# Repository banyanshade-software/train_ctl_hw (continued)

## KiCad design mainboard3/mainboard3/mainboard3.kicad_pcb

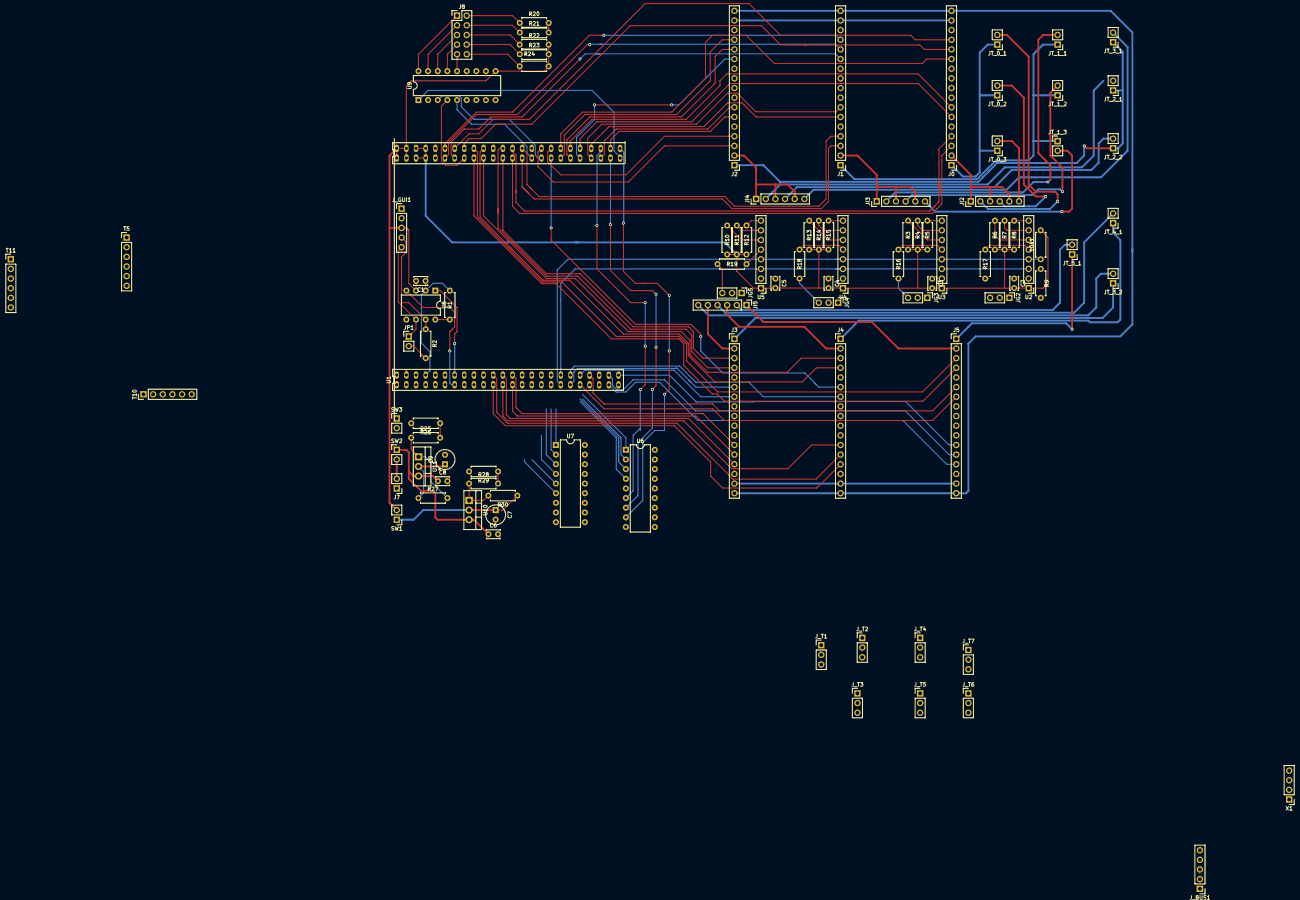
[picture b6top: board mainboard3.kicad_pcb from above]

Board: 2 copper layers, 96 parts (0 on the bottom side), 153 nets.

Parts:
10k1: R; R_Axial_DIN0207_L6.3mm_D2.5mm_P7.62mm_Horizontal
C1, C2, C3, C4, C5: 100nF; C_Disc_D3.4mm_W2.1mm_P2.50mm
C6, C8: 0.1µF; C_Disc_D3.4mm_W2.1mm_P2.50mm
C7, C9: 10µF; CP_Radial_Tantal_D5.0mm_P2.50mm
J0, J1, J2, J3, J4, J5: Conn_01x18; PinHeader_1x17_P2.54mm_Vertical
J7: Conn_01x02_Female; PinHeader_1x02_P2.54mm_Vertical
J8: Conn_02x05_Odd_Even; PinHeader_2x05_P2.54mm_Vertical
JG2, JG3, JG4, JG5: Conn_01x03_Female; PinHeader_1x03_P2.54mm_Vertical
JI2, JI3, JI4, JI5: Conn_01x06_Female; PinHeader_1x06_P2.54mm_Vertical
JP1: Jumper; PinHeader_1x02_P2.54mm_Vertical
JT_0_1, JT_0_2, JT_0_3, JT_1_1, JT_1_2, JT_1_3, JT_2_1, JT_2_2, JT_3_1, JT_3_2, JT_4_1, JT_5_1: Screw_Terminal_01x02; PinHeader_1x02_P2.54mm_Vertical
J_BUS1: Conn_01x05_Female; PinHeader_1x05_P2.54mm_Vertical
J_GUI1: Conn_01x05_Female; PinHeader_1x05_P2.54mm_Vertical
J_T1, J_T2, J_T3, J_T4, J_T5, J_T6, J_T7: Conn_01x03_Female; PinHeader_1x03_P2.54mm_Vertical
R1, R20, R21, R22, R23, R24, R25, R26: R; R_Axial_DIN0207_L6.3mm_D2.5mm_P7.62mm_Horizontal
R2: 120; R_Axial_DIN0207_L6.3mm_D2.5mm_P7.62mm_Horizontal
R3, R4, R5, R6, R7, R8, R9, R10, R11, R12, R13, R14, R15, R16, R17, R18, R19: 10k; R_Axial_DIN0207_L6.3mm_D2.5mm_P7.62mm_Horizontal
R27, R30: 240; R_Axial_DIN0207_L6.3mm_D2.5mm_P7.62mm_Horizontal
R28: 510; R_Axial_DIN0207_L6.3mm_D2.5mm_P7.62mm_Horizontal
R29: 200; R_Axial_DIN0207_L6.3mm_D2.5mm_P7.62mm_Horizontal
SW1, SW2, SW3: SW_DIP_x01; PinHeader_1x02_P2.54mm_Vertical
T5, T10, T11: Screw_Terminal_01x06; PinHeader_1x06_P2.54mm_Vertical
U1: STM32_F4xx; STM32_F4XXrev
U2, U3, U4, U5: ModuleINA3221; PinHeader_1x08_P2.54mm_Vertical
U6, U7, U9: ULN2803A; DIP-18_W7.62mm
U8: MCP2551-I-P; DIP-8_W7.62mm
U10, U11: LM317_TO220; TO-220-3_Vertical
X1: Screw_Terminal_01x04; PinHeader_1x04_P2.54mm_Vertical

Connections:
3V3: 10k1.2, C2.2, C3.2, C4.2, C5.2, R3.1, R4.1, R5.1, R6.1, R7.1, R8.1, R9.2, R10.1, R11.1, R12.1, R13.1, R14.1, R15.1, T10.2, U1.1, U1.2, U1.3, U1.4, U1.53, U1.54, U1.55, U1.56, U2.1, U3.1, U4.1, U5.1
5V: C1.2, J_BUS1.3, J_GUI1.3, R20.2, R21.2, R22.2, R23.2, R24.2, SW1.2, U1.49, U1.50, U1.51, U1.52, U8.3, U9.10, X1.3
12V: J0.17, J1.17, J2.17, J3.17, J4.17, J5.17, J_BUS1.1, J_T1.2, J_T2.2, J_T3.2, J_T4.2, J_T5.2, J_T6.2, J_T7.2, SW3.2, U6.10, U7.10, X1.1
12Vunreg: C6.1, C8.1, SW2.1, U10.3, U11.3
BOARD_LED2: U1.77, U9.5
CAN_RX: U1.13, U8.4
CAN_TX: U1.14, U8.1
CT0_1: J0.12, U1.84
CT0_2: J0.13, U1.64
CT0_3: J0.14, U1.62
CT1_1: J1.12, U1.61
CT1_2: J1.13, U1.59
CT1_3: J1.14, U1.60
CT2_1: J2.12, U1.87
CT2_2: J2.13, U1.85
CT2_3: J2.14, U1.83
CT3_1: J3.12, U1.26
CT3_2: J3.13, U1.25
CT3_3: J3.14, U1.24
CT4_1: J4.12, U1.23
CT4_2: J4.13, U1.22
CT4_3: J4.14, U1.21
CT5_1: J5.12, U1.48
CT5_2: J5.13, U1.46
CT5_3: J5.14, U1.45
GND: C1.1, C2.1, C3.1, C4.1, C5.1, C6.2, C7.2, C8.2, C9.2, J0.16, J1.16, J2.16, J3.16, J4.16, J5.16, J7.1, JG2.1, JG2.2, JG3.1, JG3.2, JG4.1, JG4.2, JG5.1, JG5.2, J_BUS1.2, J_GUI1.2, R1.1, R26.2, R29.2, T5.1, T10.1, U1.7, U1.8, U1.9, U1.10, U1.57, U1.58, U2.2, U3.2, U4.2, U5.2, U6.9, U7.9, U8.2, U9.9, X1.2
I1A: J0.2, JI2.1, JI2.3, JI2.5
I1B: JI2.2, JT_0_1.2
I2B: JI2.4, JT_0_2.2
I2C1_SCL: T5.4, T10.4, U1.15
I2C1_SDA: T5.3, T10.3, U1.16
I2C3_SCL: R9.1, U1.36, U2.3, U3.3, U4.3, U5.3
I2C3_SDA: 10k1.1, U1.35, U2.4, U3.4, U4.4, U5.4
I3B: JI2.6, JT_0_3.2
I4A: J1.2, JI3.1, JI3.3, JI3.5
I4B: JI3.2, JT_1_1.2
I5B: JI3.4, JT_1_2.2
I6B: JI3.6, JT_1_3.2
I7A: J2.2, JI4.1, JI4.3, JI4.5
I7B: JI4.2, JT_2_1.2
I8B: JI4.4, JT_2_2.2
I9B: JI4.6, JT_3_1.2
I10A: J5.2, JI5.1
I10B: JI5.2, JT_5_1.2
I11A: J4.2, JI5.3
I11B: JI5.4, JT_4_1.2
I12A: J3.2, JI5.5
I12B: JI5.6, JT_3_2.2
LED1: U1.95, U9.1
LED2: U1.47, U9.2
LED3: U1.79, U9.3
LED4: U1.63, U9.4
unnamed: C7.1, R30.1, SW1.1, U10.2
unnamed: C9.1, R27.1, SW3.1, U11.2
unnamed: J7.2, SW2.2
unnamed: J8.1, U9.18
unnamed: J8.2, R20.1
unnamed: J8.3, U9.17
unnamed: J8.4, R21.1
unnamed: J8.5, U9.16
unnamed: J8.6, R22.1
unnamed: J8.7, U9.15
unnamed: J8.8, R23.1
unnamed: J8.9, U9.14
unnamed: J8.10, R24.1
unnamed: JG2.3, R17.2
unnamed: JG3.3, R16.2
unnamed: JG4.3, R18.2
unnamed: JG5.3, R19.2
unnamed: JP1.1, J_BUS1.5, J_GUI1.5, U8.6
unnamed: JP1.2, R2.2
unnamed: J_BUS1.4, J_GUI1.4, R2.1, U8.7
unnamed: J_T1.1, U6.17
unnamed: J_T1.3, U6.18
unnamed: J_T2.1, U6.15
unnamed: J_T2.3, U6.16
unnamed: J_T3.1, U6.14
unnamed: J_T3.3, U6.13
unnamed: J_T4.1, U6.12
unnamed: J_T4.3, U6.11
unnamed: J_T5.1, U7.18
unnamed: J_T5.3, U7.17
unnamed: J_T6.1, U7.16
unnamed: J_T6.3, U7.15
unnamed: J_T7.1, U7.14
unnamed: J_T7.3, U7.13
unnamed: R1.2, U8.8
unnamed: R3.2, U3.6
unnamed: R4.2, U3.7
unnamed: R5.2, U3.8
unnamed: R6.2, U2.6
unnamed: R7.2, U2.7
unnamed: R8.2, U2.8
unnamed: R10.2, U5.6
unnamed: R11.2, U5.7
unnamed: R12.2, U5.8
unnamed: R13.2, U4.6
unnamed: R14.2, U4.7
unnamed: R15.2, U4.8
unnamed: R16.1, U3.5
unnamed: R17.1, U2.5
unnamed: R18.1, U4.5
unnamed: R19.1, U5.5
unnamed: R25.1, R27.2, U11.1
unnamed: R25.2, R26.1
unnamed: R28.1, R30.2, U10.1
unnamed: R28.2, R29.1
PWM0_1: J0.6, U1.88
PWM0_2: J0.7, U1.86
PWM1_1: J1.6, U1.90
PWM1_2: J1.7, U1.89
PWM2_1: J2.6, U1.94
PWM2_2: J2.7, U1.91
PWM3_1: J3.6, U1.37
PWM3_2: J3.7, U1.40
PWM4_1: J4.6, U1.81
PWM4_2: J4.7, U1.38
PWM5_1: J5.6, U1.42
PWM5_2: J5.7, U1.39
ROT1: T10.6, U1.44
ROT2: T10.5, U1.41
TRACK0_0: J0.1, JT_0_1.1, JT_0_2.1, JT_0_3.1
TRACK1_0: J1.1, JT_1_1.1, JT_1_2.1, JT_1_3.1
TRACK2_0: J2.1, JT_2_1.1, JT_2_2.1, JT_3_1.1
TRACK3_0: J3.1, JT_3_2.1
TRACK4_0: J4.1, JT_4_1.1
TRACK5_0: J5.1, JT_5_1.1
TURN1A: U1.18, U6.1
TURN1B: U1.20, U6.2
TURN2A: U1.11, U6.3
TURN2B: U1.12, U6.4
TURN3A: U1.43, U6.5
TURN3B: U1.92, U6.6
TURN4A: U1.93, U6.7
TURN4B: U1.96, U6.8
TURN5A: U1.27, U7.1
TURN5B: U1.28, U7.2
TURN6A: U1.30, U7.3
TURN6B: U1.29, U7.4
TURN7A: U1.33, U7.5
TURN7B: U1.34, U7.6
VSENSE0_0: J0.3, U1.73
VSENSE0_1: J0.4, U1.74
VSENSE1_0: J1.3, U1.75
VSENSE1_1: J1.4, U1.76
VSENSE2_0: J2.3, U1.80
VSENSE2_1: J2.4, U1.82
VSENSE3_0: J3.3, U1.71
VSENSE3_1: J3.4, U1.72
VSENSE4_0: J4.3, U1.67
VSENSE4_1: J4.4, U1.68
VSENSE5_0: J5.3, U1.66
VSENSE5_1: J5.4, U1.65

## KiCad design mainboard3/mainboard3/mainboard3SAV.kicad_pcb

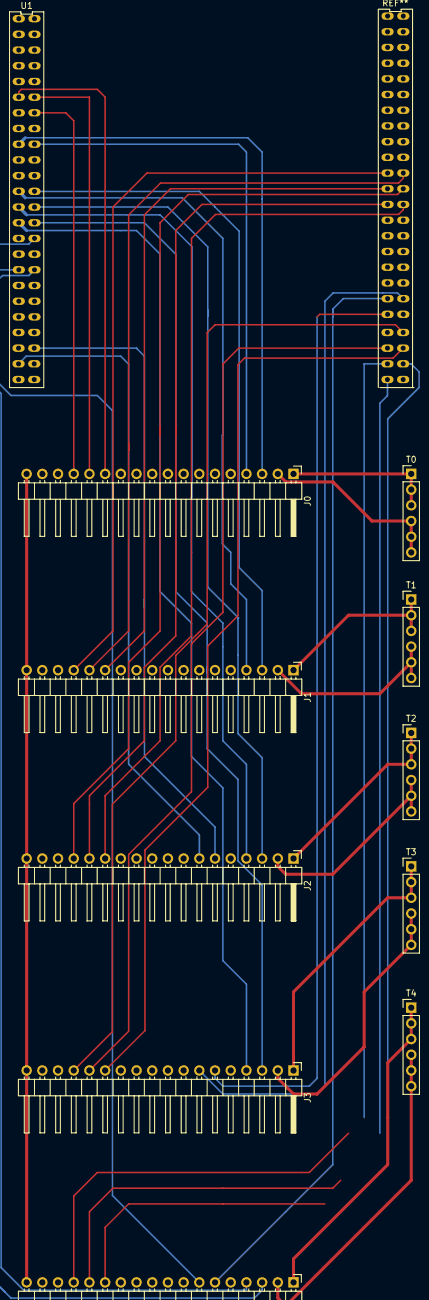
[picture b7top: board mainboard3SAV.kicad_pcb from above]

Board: 2 copper layers, 11 parts (0 on the bottom side), 47 nets.

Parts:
J0, J1, J2, J3, J4: Conn_01x18; PinHeader_1x18_P2.54mm_Horizontal
T0, T1, T2, T3, T4: Screw_Terminal_01x06; PinHeader_1x06_P2.54mm_Vertical
U1: STM32_F4xx; STM32_F4XX

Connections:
12Vunreg: J0.18, J1.18, J2.18, J3.18, J4.18
CT0_1: J0.13, U1.11
CT0_2: J0.14, U1.12
CT0_3: J0.15, U1.14
CT1_1: J1.13, U1.71
CT1_2: J1.14, U1.70
CT1_3: J1.15, U1.69
CT2_1: J2.13, U1.74
CT2_2: J2.14, U1.73
CT2_3: J2.15, U1.72
CT3_1: J3.13, U1.92
CT3_2: J3.14, U1.91
CT3_3: J3.15, U1.90
CT4_1: J4.13, U1.95
CT4_2: J4.14, U1.94
CT4_3: J4.15, U1.93
GND: J0.17, J1.17, J2.17, J3.17, J4.17
PWM0_1: J0.6, U1.37
PWM0_2: J0.7, U1.39
PWM1_1: J1.6, U1.42
PWM1_2: J1.7, U1.41
PWM2_1: J2.6, U1.44
PWM2_2: J2.7, U1.45
PWM3_1: J3.6, U1.87
PWM3_2: J3.7, U1.86
PWM4_1: J4.6, U1.85
PWM4_2: J4.7, U1.34
TRACK0_0: J0.1, T0.1, T0.2, T0.3
TRACK0_1: J0.2, T0.4, T0.5, T0.6
TRACK1_0: J1.1, T1.1, T1.2, T1.3
TRACK1_1: J1.2, T1.4, T1.5, T1.6
TRACK2_0: J2.1, T2.1, T2.2, T2.3
TRACK2_1: J2.2, T2.4, T2.5, T2.6
TRACK3_0: J3.1, T3.1, T3.2, T3.3
TRACK3_1: J3.2, T3.4, T3.5, T3.6
TRACK4_0: J4.1, T4.1, T4.2, T4.3
TRACK4_1: J4.2, T4.4, T4.5, T4.6
VSENSE0_0: J0.3, U1.17
VSENSE0_1: J0.4, U1.18
VSENSE1_0: J1.3, U1.24
VSENSE1_1: J1.4, U1.23
VSENSE2_0: J2.3, U1.26
VSENSE2_1: J2.4, U1.25
VSENSE3_0: J3.3, U1.28
VSENSE3_1: J3.4, U1.27
VSENSE4_0: J4.3, U1.30
VSENSE4_1: J4.4, U1.33
